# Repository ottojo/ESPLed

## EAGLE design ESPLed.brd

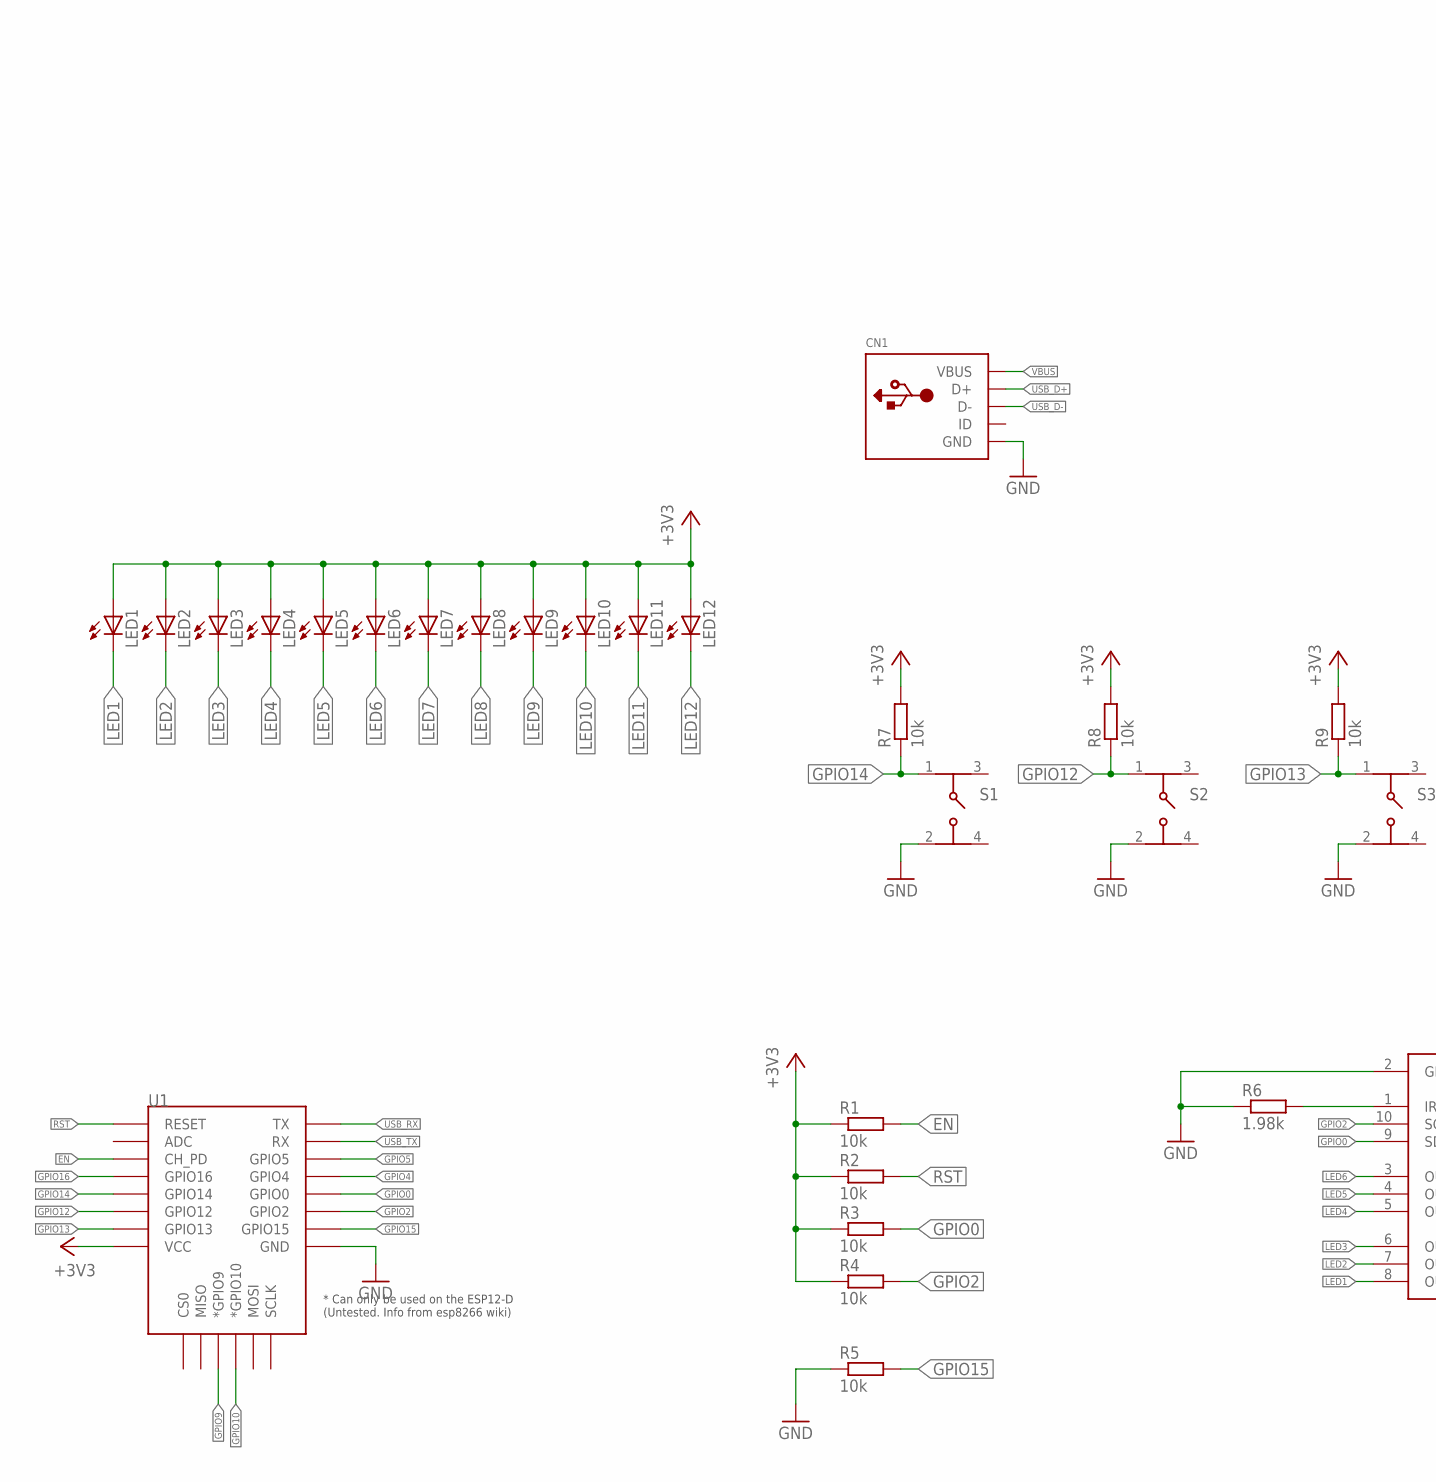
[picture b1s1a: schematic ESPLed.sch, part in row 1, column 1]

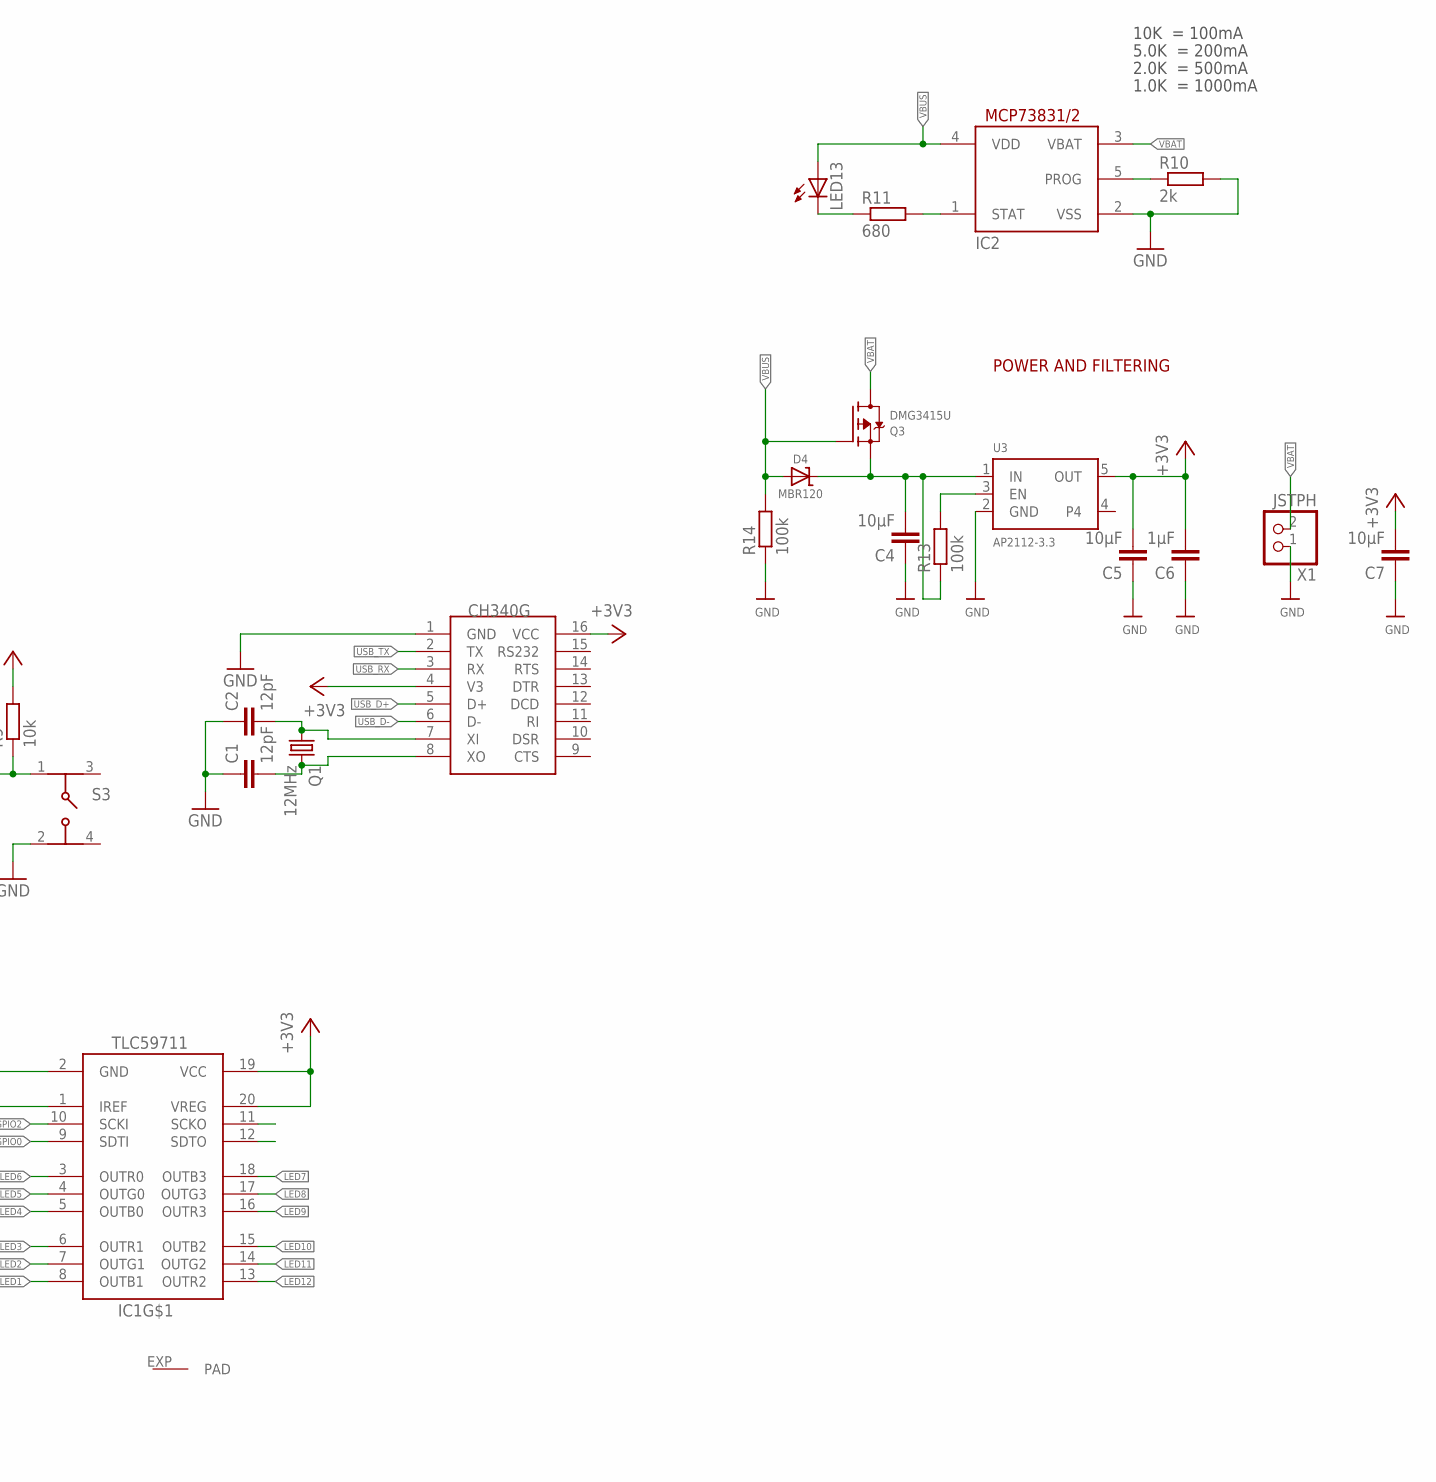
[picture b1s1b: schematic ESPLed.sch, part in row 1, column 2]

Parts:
C1, C2: 12pF; C0805
C4, C5, C7: 10µF; C0805
C6: 1µF; C0805
CN1: USBMINIB; USB-MINIB
D4: MBR120; SOD-123
IC1: TLC59711; HTSSOP20DAP
IC2: MCP73831/OT; SOT23-5L
LED1, LED2, LED3, LED4, LED5, LED6, LED7, LED8, LED9, LED10, LED11, LED12, LED13: LEDSML0805; SML0805
Q1: 12MHz; CX5032GB
Q3: DMG3415U; SOT23-R
R1, R2, R3, R4, R5, R7, R8, R9: 10k; R0805
R6: 1.98k; R0805
R10: 2k; R0805
R11: 680; R0805
R13, R14: 100k; R0805
S1, S2, S3: 4301X6XXX7X6_430156043726; 4301X6XXX7X6
U1: ESP12ESMD; ESP12E-SMD
U3: AP2112-3.3; SOT23-5
U$1: CH340G; SOIC16
X1: JSTPH; JSTPH2

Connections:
+3V3: C5.2, C6.2, C7.2, IC1.19 (VCC), IC1.20 (VREG), LED1.A, LED2.A, LED3.A, LED4.A, LED5.A, LED6.A, LED7.A, LED8.A, LED9.A, LED10.A, LED11.A, LED12.A, R1.1, R2.1, R3.1, R4.1, R7.2, R8.2, R9.2, U1.VCC, U3.5 (OUT), U$1.4 (V3), U$1.16 (VCC)
EN: R1.2, U1.CH_PD
GND: C1.1, C2.1, C4.1, C5.1, C6.1, C7.1, CN1.GND, IC1.2 (GND), IC2.2 (VSS), R5.1, R6.1, R10.2, R14.1, S1.2, S2.2, S3.2, U1.GND, U3.2 (GND), U$1.1 (GND), X1.1
GPIO0: IC1.9 (SDTI), R3.2, U1.GPIO0
GPIO2: IC1.10 (SCKI), R4.2, U1.GPIO2
GPIO4: U1.GPIO4
GPIO5: U1.GPIO5
GPIO9: U1.GPIO9 (*GPIO9)
GPIO10: U1.GPIO10 (*GPIO10)
GPIO12: R8.1, S2.1, U1.GPIO12
GPIO13: R9.1, S3.1, U1.GPIO13
GPIO14: R7.1, S1.1, U1.GPIO14
GPIO15: R5.2, U1.GPIO15
GPIO16: U1.GPIO16
IN: C4.2, D4.C, Q3.2 (S), R13.1, U3.1 (IN)
IREF: IC1.1 (IREF), R6.2
LED1: IC1.8 (OUTB1), LED1.C
LED2: IC1.7 (OUTG1), LED2.C
LED3: IC1.6 (OUTR1), LED3.C
LED4: IC1.5 (OUTB0), LED4.C
LED5: IC1.4 (OUTG0), LED5.C
LED6: IC1.3 (OUTR0), LED6.C
LED7: IC1.18 (OUTB3), LED7.C
LED8: IC1.17 (OUTG3), LED8.C
LED9: IC1.16 (OUTR3), LED9.C
LED10: IC1.15 (OUTB2), LED10.C
LED11: IC1.14 (OUTG2), LED11.C
LED12: IC1.13 (OUTR2), LED12.C
unnamed: LED13.C, R11.1
PROG: IC2.5 (PROG), R10.1
RST: R2.2, U1.RESET
STAT: IC2.1 (STAT), R11.2
USB_D+: CN1.D+, U$1.5 (D+)
USB_D-: CN1.D-, U$1.6 (D-)
USB_RX: U1.TXD0 (TX), U$1.3 (RX)
USB_TX: U1.RXD0 (RX), U$1.2 (TX)
VBAT: IC2.3 (VBAT), Q3.3 (D), X1.2
VBUS: CN1.VBUS, D4.A, IC2.4 (VDD), LED13.A, Q3.1 (G), R14.2
VREG_EN: R13.2, U3.3 (EN)
XI: C2.2, Q1.P$1 (1), U$1.7 (XI)
XO: C1.2, Q1.P$2 (2), U$1.8 (XO)

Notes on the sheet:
10K = 100mA
5.0K = 200mA
2.0K = 500mA
1.0K = 1000mA
POWER AND FILTERING

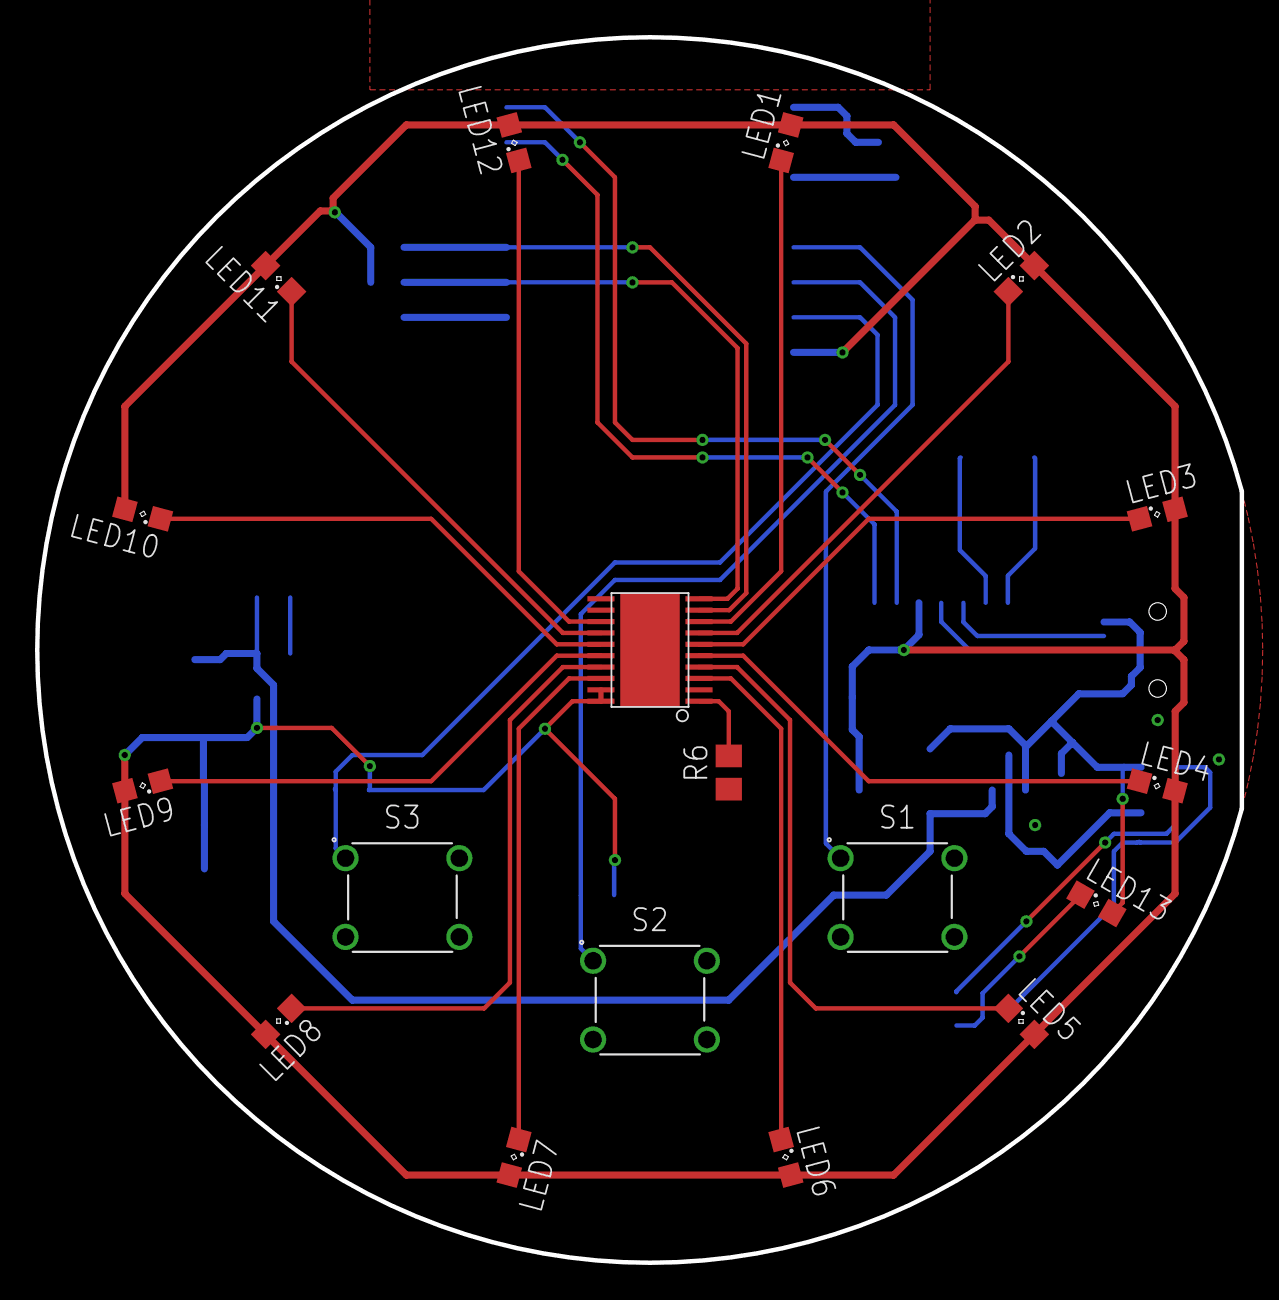
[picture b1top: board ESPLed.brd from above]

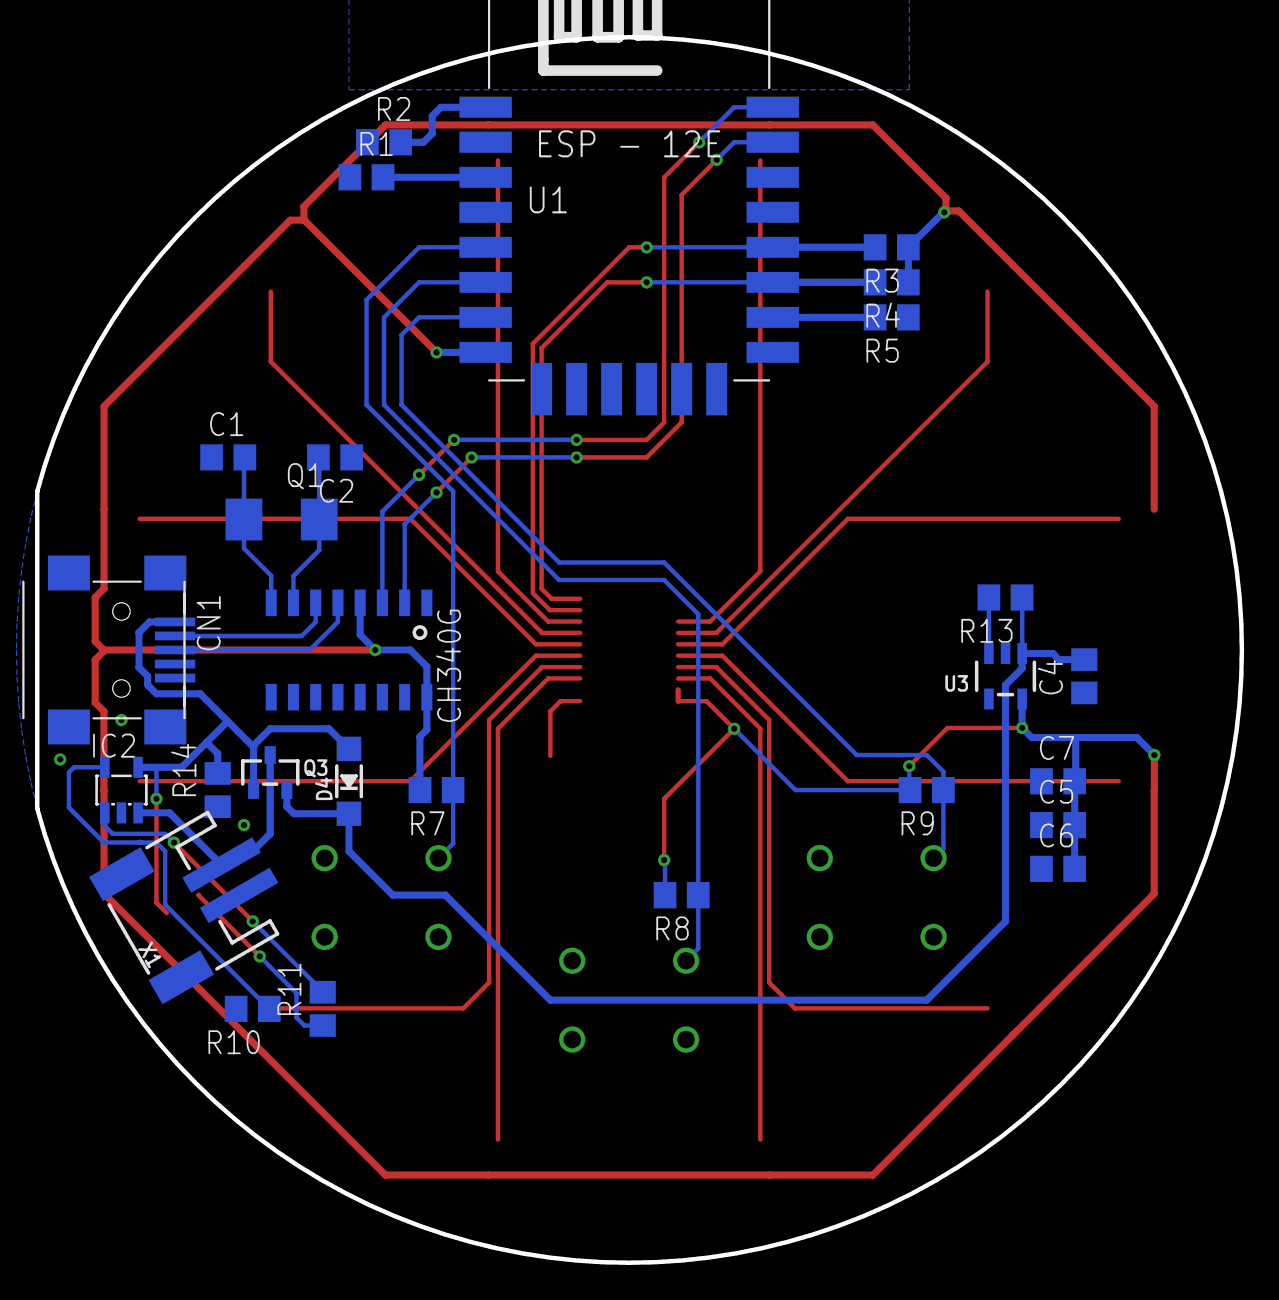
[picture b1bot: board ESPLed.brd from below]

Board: 2 copper layers, 68.8 x 70.0 mm, 45 parts (27 on the bottom side), 36 nets.

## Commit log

2017-06-03 buttons, usb
2017-06-15 lipo charging

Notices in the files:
parts and their libraries:
Wurth_Elektronik_Electromechanic_Switch_: Copyright: Würth Elektronik
microbuilder: This work is placed in the public domain, and may be freely used for commercial and non-commercial work with the following conditions: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
